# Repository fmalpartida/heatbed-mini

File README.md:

# heatbed-mini
Mini heatbed for small footprint 3D printers. This bed has been designed for the lewihe play but can be retrofitted to other small 
printers with a print area of 100x100 mm.

## Specifications

+ **Size:** 100x100 mm
+ **Rated voltage:** 12V
+ **Maximum operational temperature:** 150ºC
+ **Power dissipation:**
   + **Rev B:** 69W aprox: 12V @25ºC, 50W aprox: 12V @110ºC 
+ **Resistance:**
   + **Rev B**: 2.1 Ohms aprox, 2.8 Ohms aprox @110ºC
 
Do not exceed rated parameters.

## Images

## License
Released under CERN Open Hardware License v1.2
http://www.ohwr.org/attachments/2388/cern_ohl_v_1_2.txt

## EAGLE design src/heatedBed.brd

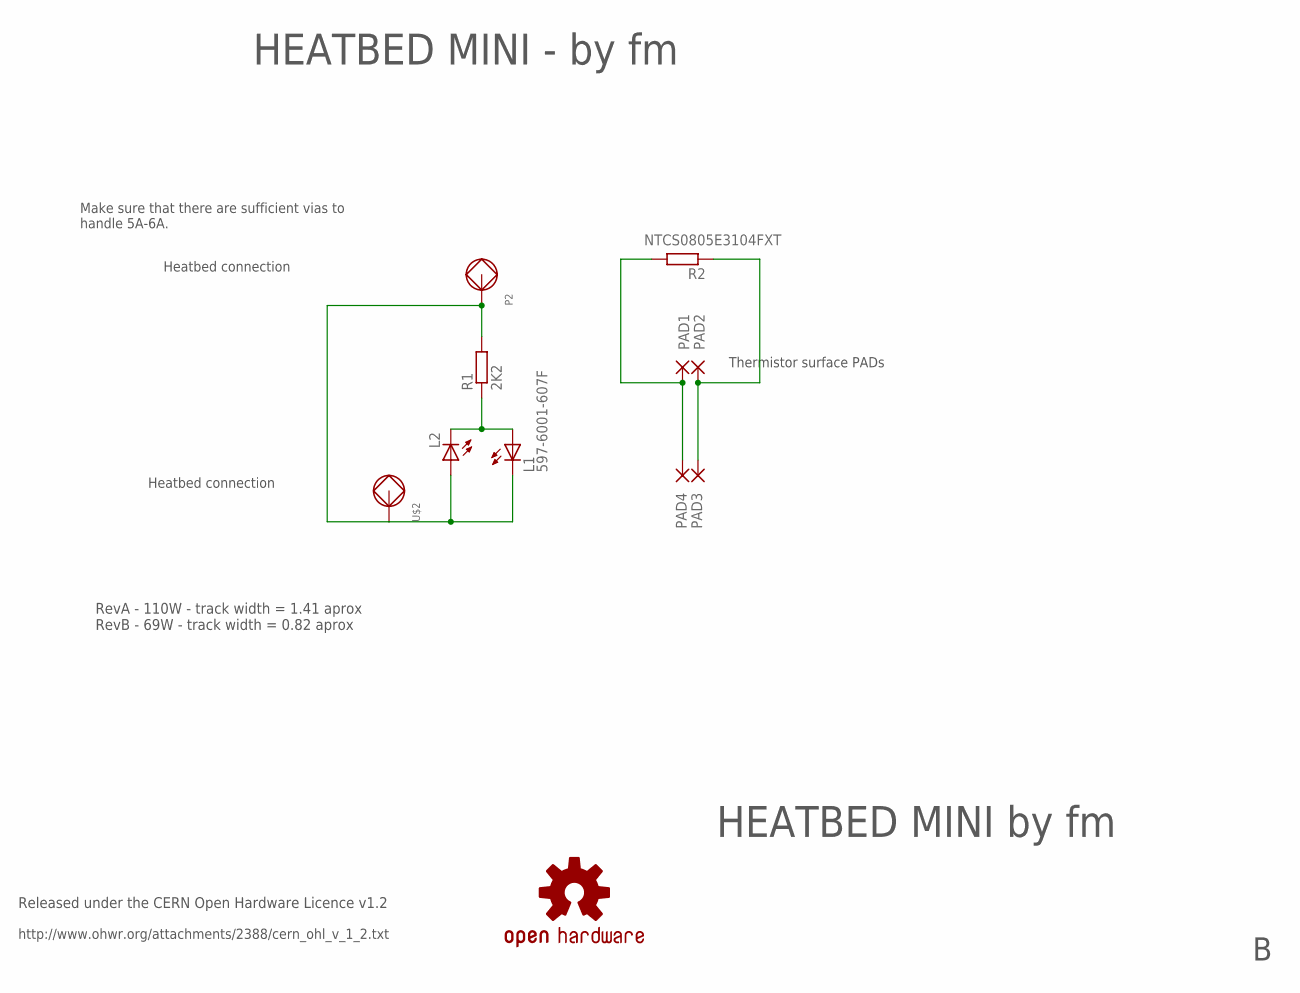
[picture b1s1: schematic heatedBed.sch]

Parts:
L1: 597-6001-607F; CHIPLED_1206_REVERSE
L2: LEDCHIPLED_1206_REV; CHIPLED_1206_REVERSE
P2: LONG_PAD
PAD1, PAD2, PAD3, PAD4: SMD5; SMD2,54-5,08
R1: 2K2; R0805
R2: NTCS0805E3104FXT; R0805
U$2: LONG_PAD
U$5: SPARKFUN_OSHW-LOGOL; SPARKFUN_OSHW-LOGO-L

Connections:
unnamed: PAD1.1, PAD4.1, R2.2
unnamed: L1.A, L2.C, R1.1
unnamed: PAD2.1, PAD3.1, R2.1
P1: L1.C, L2.A, P2.P$1, P2.P$2, P2.P$3, R1.2, U$2.P$1, U$2.P$2, U$2.P$3

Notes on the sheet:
Released under the CERN Open Hardware Licence v1.2
HEATBED MINI by fm
Heatbed connection
Make sure that there are sufficient vias to handle 5A-6A.
Thermistor surface PADs
http://www.ohwr.org/attachments/2388/cern_ohl_v_1_2.txt
HEATBED MINI - by fm
RevA - 110W - track width = 1.41 aprox RevB - 69W - track width = 0.82 aprox

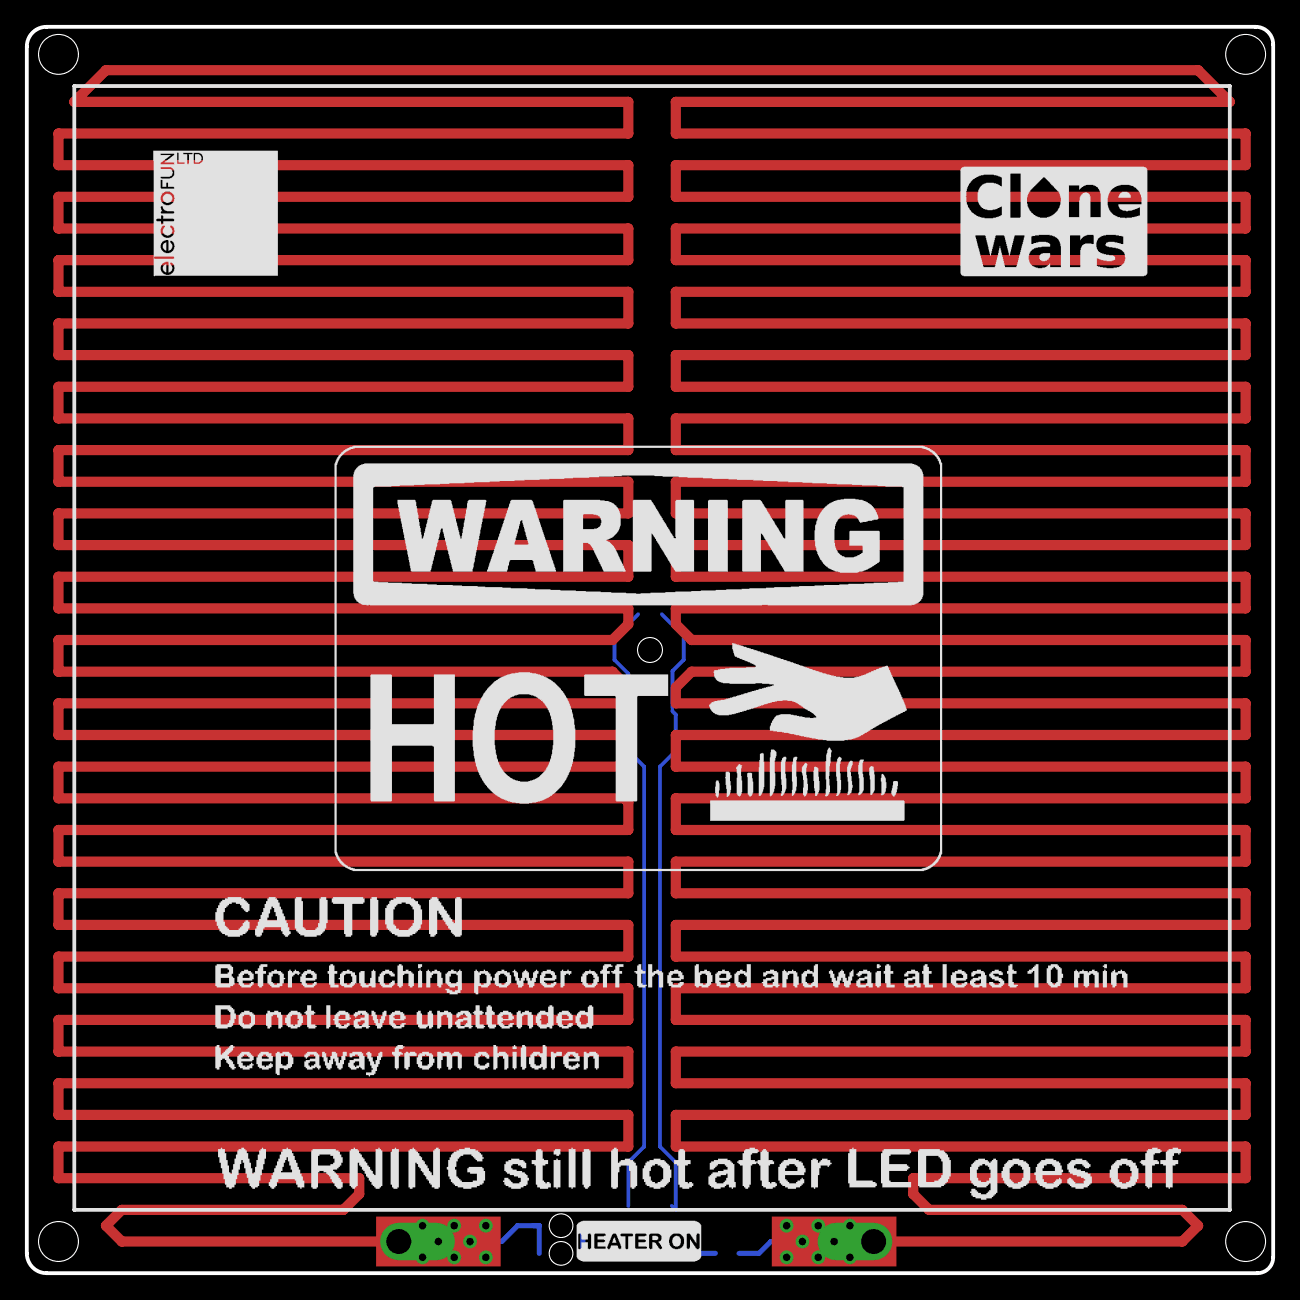
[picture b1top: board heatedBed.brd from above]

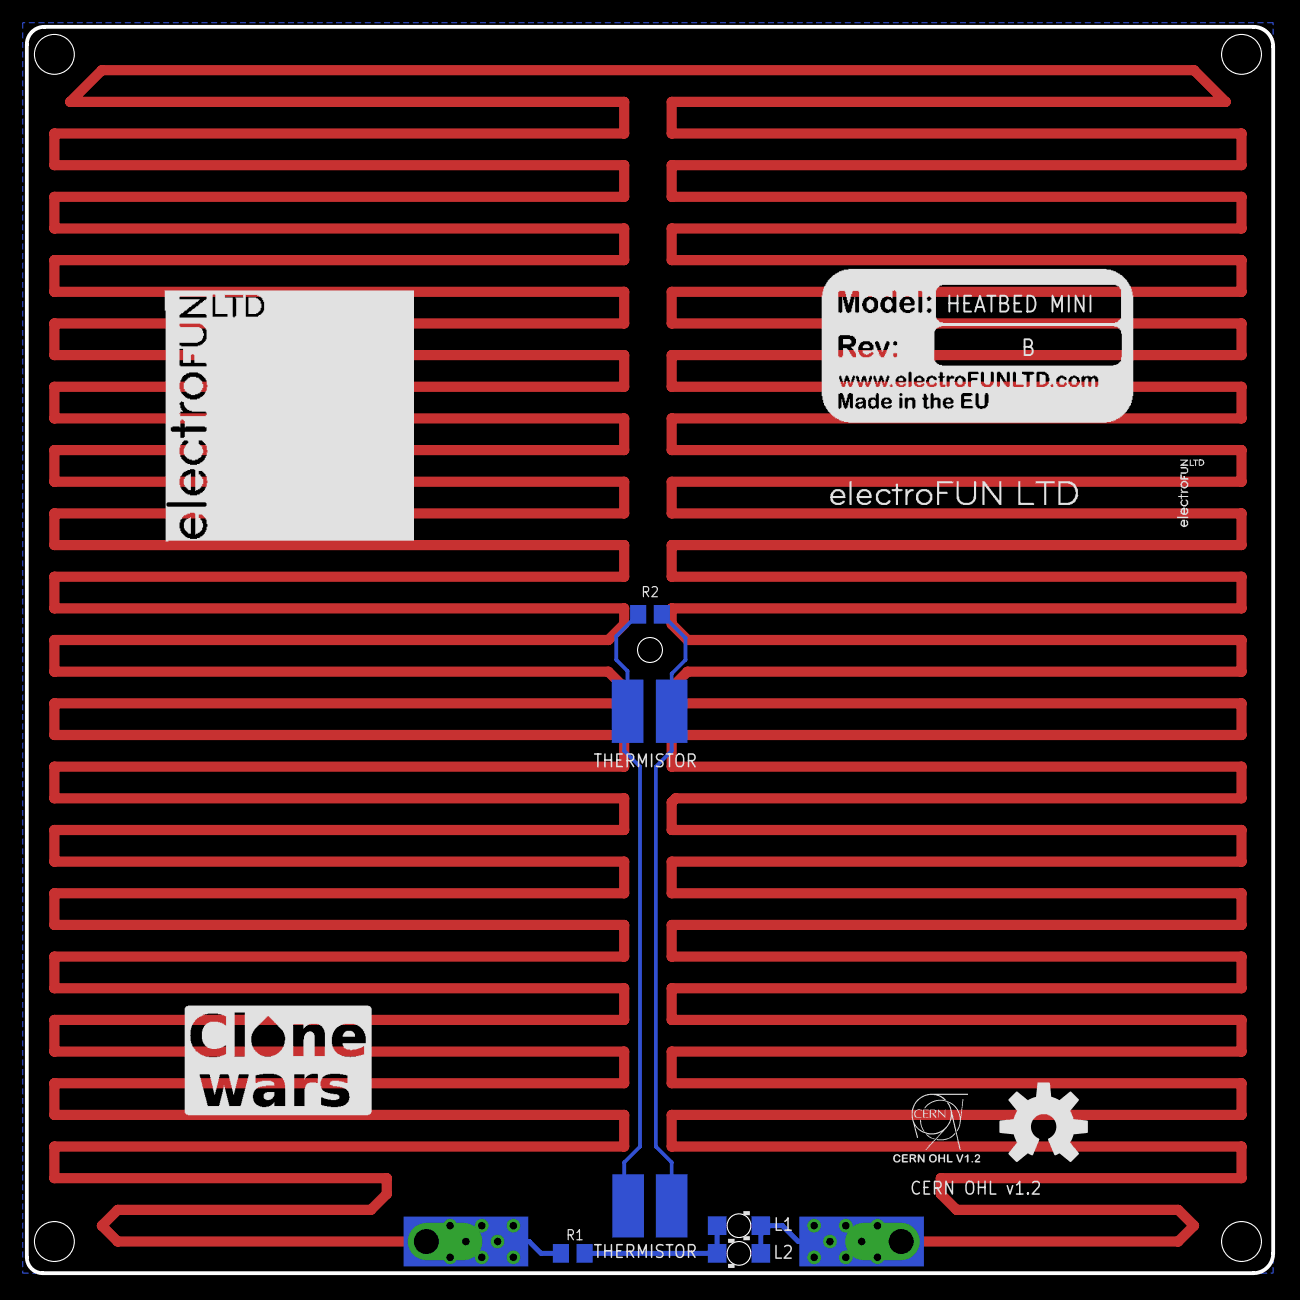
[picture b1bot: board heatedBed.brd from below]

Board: 2 copper layers, 100.0 x 100.0 mm, 21 parts (14 on the bottom side), 4 nets.

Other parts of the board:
U$1: CAUTION
U$3, U$7: CLONE_WARS
U$4: CERN_OHL
U$6: ELECTROFUN_STRIP
U$8: BOARD_REF
U$9: HEATERON
U$10: WARNING_HOT
U$11: ELECTROFUN_20X20
U$12: ELECTROFUN_10X10

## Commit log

2015-08-18 First version of the mini heatbed for the lewihe play.
2015-08-18 Organized folder structure and added images to the repository.
2015-08-18 Added images to readme file.
2015-08-18 Updated PCB for bottom mount LEDs
2015-08-18 Updated silk screen for production prototype run.
2015-08-18 Update schematic pdf file.
2015-08-18 Updated schematic with boar revision and arrangement.
2015-08-19 Added board dimensions and modified drill sizes.
2015-08-19 Update README.md
    Added dimension drawing.
2015-09-07 Added images to the repo.
2015-09-07 Preparing to release revision A. Included gerber files
2015-09-07 Update README.md
    Corrected wiki typo.
2015-09-07 Prepare Rev B release.
2015-09-08 Prepared for Rev B.
2015-09-08 Updated revision B files.
2015-12-11 Updated files for RevB.
2015-12-11 Added 3D parts to fit heated.
